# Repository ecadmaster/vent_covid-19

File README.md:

# vent_covid-19
Respirador para atención a pacientes con COVID_19

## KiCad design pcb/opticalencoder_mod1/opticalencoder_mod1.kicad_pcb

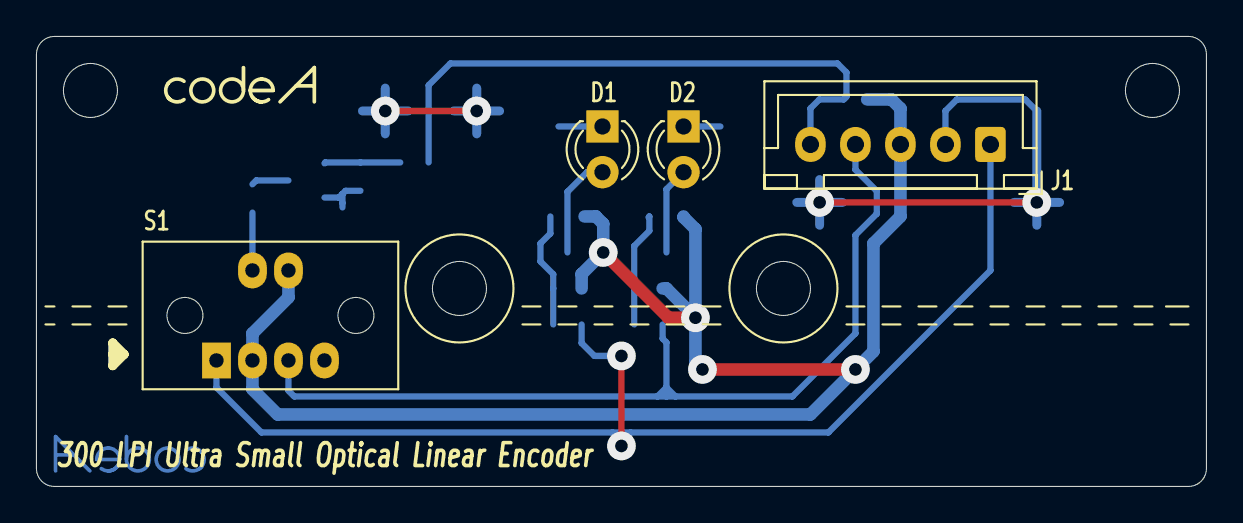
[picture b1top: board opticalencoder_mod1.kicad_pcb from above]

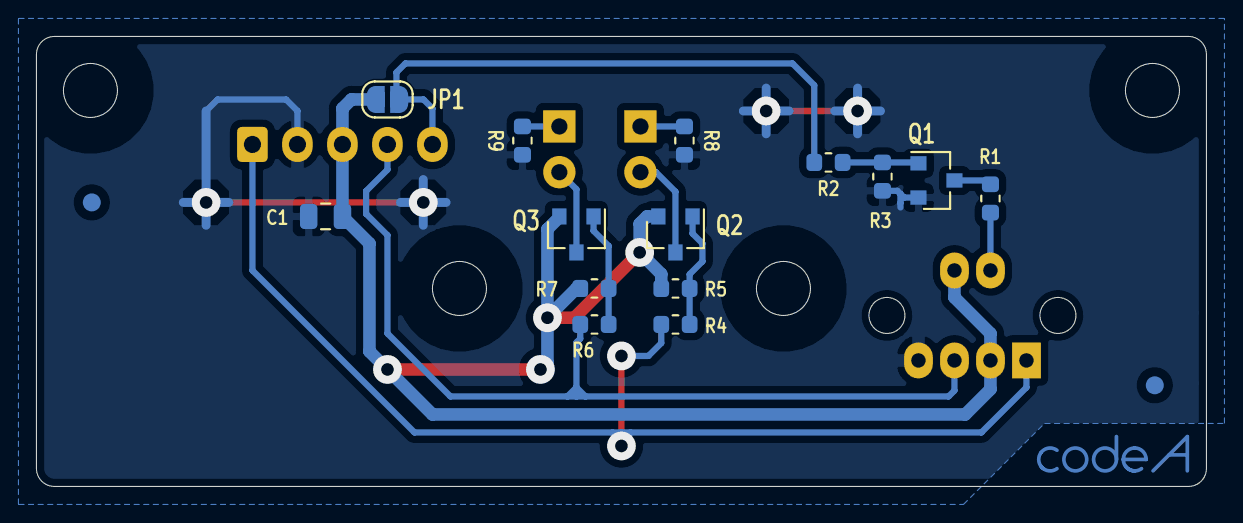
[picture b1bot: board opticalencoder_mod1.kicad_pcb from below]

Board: 2 copper layers, 65.0 x 25.0 mm, 26 parts (17 on the bottom side), 14 nets.

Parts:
C1: 100nF; C_0805_2012Metric
D1: chA; LED_D3.0mm
D2: chB; LED_D3.0mm
FID1, FID2: Fiducial; Fiducial_1mm_Mask2mm
G1: codeA_Logo; codeA-logo_Copper
H1: MountingHole_SideL; MountingHole_3mm
H2: MountingHole_SideR; MountingHole_3mm
H3: MountingHole_CenterL; MountingHole_3mm
H4: MountingHole_CenterR; MountingHole_3mm
J1: Conn_Port; JST_XH_B5B-XH-A_1x05_P2.50mm_Vertical
JP1: LED_Enable; SolderJumper-2_P1.3mm_Open_RoundedPad1.0x1.5mm
Q1: MMBT3904; SOT-23
Q2, Q3: MMBT3906; SOT-23
R1: 220R; R_0603_1608Metric
R2, R3, R4, R5, R6, R7: 4K7; R_0603_1608Metric
R8, R9: 2K; R_0603_1608Metric
S1: Agilent_AEDS-962x; Agilent_AEDS-962x_Vertical
codeA-logo_Silk: VAL**; codeA-logo_Silk

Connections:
+3V3: C1.1, J1.3, JP1.1, Q2.2, Q3.2, R5.1, R7.1, S1.2, S1.5
GND: C1.2, J1.2, Q1.2, R3.1, R8.2, R9.2, S1.4
unnamed: D1.1, R8.1
unnamed: D1.2, Q2.3
unnamed: D2.1, R9.1
unnamed: D2.2, Q3.3
unnamed: Q1.1, R2.1, R3.2
unnamed: Q1.3, R1.2
unnamed: Q2.1, R4.1, R5.2
unnamed: Q3.1, R6.1, R7.2
unnamed: R1.1, S1.6
chA: J1.1, R4.2, S1.1
chB: J1.4, R6.2, S1.3
ledEN: J1.5, JP1.2, R2.2

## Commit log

2020-04-05 First release, opticalencoder_mod1 (pcb)
2020-04-07 minor fix, B & E inverted on Q2 & Q3
2020-04-09 init, vent-control-nano (pcb)
2020-04-09 init, ven-control-nano (firmware, v0)
2020-04-09 fix, .gitignore
2020-04-10 adding license
